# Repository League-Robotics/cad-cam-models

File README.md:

# Geared grippers

Two-jaw LEGO-compatible grippers driven by a pair of meshing 24T gears. The
gears are molded into short **gear arms** that stay in the frame. The jaws are
swappable **extension arms** that pin onto each gear arm's stub with two 2L
LEGO friction pins, 16 mm (2 studs) apart. The pins point at the other jaw, so
gripping pushes the arm further onto them.

## Printable parts: `grippers/`

| Folder | What | Parts |
|---|---|---|
| `arms/` | The gear arms on LEGO axles, shared by every set | `left_arm` (the Nezha motor's driven arm, cross hub), `right_arm` (the idler arm of every set: one plain 4.95 round hole, it turns on the axle the frame holds in cross holes; `idler_hub_pins` brings the four hub pin holes back) |
| `nezha/` | Gripper on the Nezha motor; uses both `arms/` | `frame` |
| `servo_standard/` | Gripper on a standard-size hobby servo; idler is `arms/right_arm` | `spline_arm`, `frame` |
| `servo_9g/` | Gripper on a 9 g micro servo; the frame top is a 3 × 5 block of pin holes, and the idler runs on a 3L axle; idler is `arms/right_arm`. `frame_centred` is the 2026-10-28 revision (`centred = true`): hole grid centred on the jaws (6 columns, the mesh on the 4th), full-unit back wall with 4 rows × 6 holes, the top plate a row longer with 6 holes out of its front face | `spline_arm`, `frame`, `frame_centred` |
| `extensions/` | Swappable arms; fit every set | `can_arm`, `cube_arm`, `cube_low_arm`, `cube_short_arm`, `ball_arm`, each `_left` and `_right` |
| `plates/` | One sheet of parts with first-layer sprues | `all_parts` |
| `brick_frame/` | The cage round the Nezha brick (`scad/brick_frame.scad`, 2026-11-02): four flat prints, each on its outer face, put together with 11 2L pins | `plate` (all four on one bed, 122 x 114), or one at a time: `side_j`, `side_iic`, `end_bar` (print two) |
| `pi_frame/` | The open frame round a Raspberry Pi (`scad/pi_frame.scad`, 2026-11-03): five flat prints, 8 2L pins; weld the Pi onto the base's posts | `plate` (all five on one bed, 114 x 164), or `base`, `window` (print two), `top_bar` (print two) |
| `huskylens_case/` | The LEGO tray for the DFRobot HuskyLens (`scad/huskylens_case.scad`, first draft 2026-11-14): one print, back face down, no supports; `views.png` is its four-view | `huskylens_case` |

Every STL is already in print orientation. The driven arm differs by motor
only in its hub: a LEGO cross-axle hole (`arms/left_arm`, Nezha) or a press-fit
spline socket (each servo set's `spline_arm`; the 9 g one is a plain 4.65 mm
hole). The idler arm is the same `arms/right_arm` everywhere.

- **Left / right:** the left extension arm goes on the driven gear arm (motor
  or spline), the right one on the idler arm.
- **Ball arms** stand on the cup and need supports under their base.
- **Cube arms** print on their outer face with the texture up.
- **Can arms** print flat.

| Arm | Holds | Closed at 0° |
|---|---|---|
| can | 66 mm can | 65 mm ring |
| cube | 26 mm foam cube | parallel paddles, 26 mm apart |
| cube_low | 26 mm foam cube, near the floor | as cube, but an open "racket" paddle (rim + diagonal ribs) 50 long × 62 tall: 16 mm further down and 8 up; swap left and right to put the 8 mm end down. On the Nezha frame it clears to ~29° open |
| cube_short | 26 mm foam cube, low mounts | as cube, paddle 32 tall (3 mm off each end), for mounts where the full paddle would reach the floor |
| ball | 40 mm ball | cylindrical cups, R 20.5 |

Clear opening, checked against frame and motor/servo for all three arms:

- Servo frames (standard and 9 g): 66°
- Nezha frame: 60°

## Viewing assemblies in the browser

`bash tools/make_views.sh [servo9g|nezha|plate] --open` builds self-contained
3D viewer pages in `view/` (three.js, STLs embedded, works from file://), one
checkbox and colour per component, and opens them in Chrome. Each assembly's
`show` parameter exports one component in place; `tools/mockup_html.py` (a part named with a leading `-` starts unticked, e.g. the can arms; a `pivot=x,y,sign` option makes it turn about that vertical axis with the Jaws slider) puts
them on one page. `bash tools/serve_views.sh` serves `view/` on http://127.0.0.1:8768/ so a page opens in VS Code's Simple Browser (file:// pages open as text there). `tools/bottom_view.py PART.stl OUT.svg` draws a part from
below on the 8 mm cell grid, for marking up changes.

## Sources

Carvera parts are moving to `/Volumes/Proj/proj/robot-projects/carvera/design/`
(read its `AGENTS.md`). The camera bracket (was `carvera_angle.scad`) and the
two-camera laser mount (was `laser_cam_mount.scad`) the dust-bay plate
(was `carvera_pi_bin.scad`) and the USB hub rack (was `usb_hub_rack.scad`) moved
there on 2026-11-06.

`scad/` holds the OpenSCAD sources:

| File | What |
|---|---|
| `gripper.scad` | Gear sector, original ring arm, Nezha 1U frame (library) |
| `swap_gripper.scad` | Gear arms (`nub` in the code) and the can / cube / ball extension arms. The can ring's rear ends (where it completes the circle inboard of the beam) are cut flat `ring_trim` (3.1) up from their lowest point so the closed arms clear the Cutebot gripper's caster beam (2026-10-29; 0 for the full ring), the cut meeting the base's inner face with a `ring_trim_r` (2) fillet. The ring is turned `can_ring_rot` (15) on the arm and then `can_ring_open` (5) about the axle relative to the stub (2026-10-29: the halves concentric with the arms 5 open), so gripper.scad's unchanged tips (10 mm thinned on opposite faces) meet on the centre line at theta 6.8, the halves are concentric at 5 and the tips lap fully at 4.3, the closing limit (past it the thick parts jam; the lap grows 3.9 mm per degree); `view/cutebot_can_ring.png` shows the ring closing |
| `nezha_gripper.scad` | Nezha set: assembly, parts, `clash` check |
| `servo_gripper.scad` | Servo sets (`servo = "standard"` or `"9g"`): assembly, parts, `clash` check; `jaw = "ring"` gives the old one-piece arms. `centred = true` (9 g, 2026-10-28, used by the block and Cutebot grippers): the hole grid centred on the gear mesh (`grid_z`, 6 columns about `mesh_z`; the axles sit 1.5 units off it, so the axle row keeps only the holes 12 from an axle), the wall behind the arm layer a full unit (`wall_t`) with a 4th row of holes (`lego_y`), the top plate's rows 3.9 in from the back face (`top_rows_x`: the axles 1.9 ahead of the first) and its front face one row further out at the gear teeth's reach, with blind holes (`front_hole_depth`, `front_skip`) in it for a caster or a part pinned on ahead. The default keeps the original frames unchanged |
| `lever_gripper.scad` | CONCEPT (2026-10-26): gearless gripper on a horizontal 9 g servo. Servo on edge, shaft forward between the jaw axles; vertical double horn with a ball on each tip; each jaw is a lever on a vertical axle with the swappable-arm stub and a fore-aft fork that straddles its ball (left jaw's fork over the upper ball, right jaw's under the lower one; both jaws are one part turned over). `phi` is the servo angle (-45 closed, +45 open, 53 deg of jaw); `show` = "all", "jaw", "clash", or one component. Pictures: `view/lever_gripper_concepts.png` (four concepts), `view/lever_gripper_mockup.png`, viewer `view/lever_gripper.html` |
| `swap_plate.scad` | The all-parts plate layout |
| `swap_plate_sprues.scad` | The plate's sprue bars (generated) |
| `lego.scad` | Include this for any LEGO Technic feature: pulls in `lib/Technic.scad` ([cfinke/Technic.scad](https://github.com/cfinke/Technic.scad): beams, pins, axles, connectors, gears) and adds `technic_pin_hole()` (exact LEGO hole, for models of real parts) and `pd_pin_hole()` / `pd_axle_hole()` (print-tuned holes from the League's Part Designer, lego3d.jointheleague.org; use these on anything we print) |
| `reflectance_sensor.scad` | The robots' 4-channel reflectance sensor with its LEGO brackets, from a scan (`models/reflectance_sensor_top_scan.stl` is a later scan of the board's top face, registered to the same coordinates on the bracket holes) (`part = "overlay"` shows `models/reflectance_sensor_scan.stl` over it); `pin_holes()` and `rs_holes` for parts that mount to it; the four cans' positions are from the top scan's solder-pad columns (2026-10-29), their TCRT5000 size from a photo |
| `front_plate.scad` | Sensor plate with the 9 g gripper frame built onto its front. Exact geometry only where something mates: the horns (the two beams into the robot), the gripper frame (arm bearing, pivot, idler axle, the servo's tab legs), the pin holes, the casters' seats, and pockets under the frame floor for what stands on the board's top (the sensors' clips, the button, two solder rows), measured on `models/reflectance_sensor_top_scan.stl`. Everything else is `models/front_plate_body.stl`, made by `tools/front_plate_body.py`: a smoothed hull-like lid with filleted posts down to the sensor, and the cable U, arm sweep and caster spaces carved out with rolled edges (re-run it with `uv run tools/front_plate_body.py` after moving anything it wraps). `part = "required"` shows the mating surfaces alone; `part = "control"` is just the control surfaces (the gripper frame, the horns, the servo tab seat, the sensor pads on the side brackets (pinned) and middle bracket (flat: the jack covers its holes), the caster seats, holes cut; print file `grippers/sensor_plate/control_surfaces.3mf` / `.stl`, `part = "control_print"`); `part = "clash_*"` checks it. Two LEGO EV3 ball casters (`models/ev3_ball_caster/`, SquareD's model, thing:622701, CC BY-SA) turned 90 degrees, slide on from the sides onto pins into seats beside the cable, set `caster_drop` (5 mm) below the robot's floor line so they bear on every robot Print files: `grippers/sensor_plate/front_plate_print.3mf` (clean manifold; prefer it) and `.stl`, frame floor down on the bed, support under the deck and horns |
| `robot_plate.scad` | The bought 11 x 19 Technic panel plate (LEGO 39369's shape: pin holes through every cell, a horizontal hole in from the face at every even cell round the edge) with the cut for the reflectance sensor, exactly on the cell edges: `hole = "3x4"` (columns 5-7, rows 5-8; the sensor under the plate, pinned at row 4 with its jack up through the hole and its PCB edge at the plate's front edge), `"3x3_9"` (the default and the one cut since 2026-10-30: 3x3 at rows 9-11, the sensor pinned at row 8; the user walked the hole back from 5-8 over four plates), `"cans"` (the sensor standing on top of the plate on its brackets, pinned at row 5 from below, with a pocket through the plate for its cans, one row behind the front so row 1's holes stay free, the middle two cans sharing one pocket since the 4.2 web between them did not survive the first cut, and the pockets' front edge 1.5 further forward (`can_front_ext`) since the cans did not clear it, the back edge 0.5 further back (`can_back_ext`) (2026-10-30); the cans at x = +-6 and +-30, 20.45 ahead of the bracket row, on the solder-pad columns of the top scan (2026-10-29), the body size still a guess, so `can_clear` is 1.0) or `"3x3"` (rows 6-8, the plate cut so far; its job ran 1.65 past the front cell edge, which is dropped). Cells count from the front-left corner, the plate held with its 19 side up and down. `part = "assembly"` puts the sensor in place; `"cam"` is the plate in the Carvera job's coordinates. Drawing: `view/robot_plates_drawing.png` (`tools/plate_drawing.py`), viewer `view/robot_plates.html` |
| `caster_post.scad` | The caster post (2026-10-28): a separate flat print for the grippers that stand on the EV3 ball caster ahead of the jaws (since 2026-10-29 every stance of the block gripper and the Cutebot gripper has one, its name etched in its top). Its back face is the centred frame's front face (the gear teeth's reach); two blind pin holes mate with the floor's front-face holes at x = +-8, two more in its front take the caster's pins; the post is a box from the floor's bed face or the beam's bottom up to the beam's top or the floor's top, with a pocket in its front for the caster's housing, which widens behind the beam face below the beam (`housing_prof`, from the caster model; the user measured its widest, 8.3), and `post_depth_for(floor_z, caster_top_z, min_depth)` makes it as shallow as the mating holes allow: `pin_wall` (0.8) between their bottoms and the pocket, or 8 + wall + 8 when they share a height band with the caster's pin holes (16.8), and at least `min_depth`: `post_min_depth(arm_z, caster_top_z)` gives `ring_post_depth` (17) when the beam is in the arm layer, which the closed can arms' trimmed ring ends need (so 17.0 on the Cutebot and the low stance, 17.55 on front, where the housing wants more). Also the caster model, `caster_on_post`, a 2L pin model and the mating pins. `caster_post(y_face, floor_z, pin_x, caster_top_z, min_depth, label)` in place, `caster_post_print` on its back face (every hole vertical) |
| `block_gripper.scad` | The 9 g gripper on the front of the two-plate robot (plates 3 units apart on the Nezha motors), since 2026-10-29 built from the Cutebot gripper's pieces: three flat prints pinned with 2L pins and glued. The frame is the centred 9 g frame turned over (the same print as the Cutebot's, unlabelled: floor of pin holes ahead of the robot, jaws centred on the plate with the axles at x = +-12, a full-unit back wall with 4 rows x 6 columns of holes facing the robot). The block (5 wide x 3 deep x 2 high; 3 with `sensor_mount = "under"`) sits between the plates on the front 3 rows, 10 pin holes down through its back two rows into the top plate (and the bottom plate when 3 high), and its front row given over to two rows of 5 blind holes in its front face that pin into two of the frame's wall rows. The frame's height is which wall rows meet the block's (`stance`: rows 8 apart, so the old 0 / 4.15 / 15.4 drops became 1 / 9 / 17): `"level"` the 2nd and 3rd rows (wall top 43, the floor 0.9 below flush, the top row pins into the top plate's edge holes at x = 0, +-16; cube paddles 16.4 off the ground), `"low"` the top two rows (wall top 35; the bottom row into the bottom plate's edge holes; paddles 8.4), `"front"` the top row on the block's lower row (wall top 27; the 3rd row into the bottom plate's edge holes; paddles 0.4). The caster post (`caster_post.scad`, one per stance with its name etched) pins into the floor's front-face holes at x = +-8 with the caster's beam top 28 over the ground: 16.8 / 17.0 / 17.55 deep. The can arms close clear of the caster in level and low (checked at theta 5 and 4.3); not in front, where the arm layer is under the beam and the ring's rear ends hit the housing's flare however the post is placed, so front is for the cube paddles. `sensor_mount = "top"` (the cans plate, the default; the block clears the sensor's parts) or `"under"` (the 3x4 plate). `part = "frame"` / `"block"` / `"post"` in place, `"print_*"` on the bed, `"clash"` / `"arm_clash"` / `"fit"` / `"caster_fit"` / `"block_fit"` check the arms / the arms against each other / the sensor / the caster / the block (`"clash_view"`, `"ring_view"` as the Cutebot's); `show` exports each component in place; `tools/robot_pics.py` makes `view/block_gripper_stances.png` (the three stances, labelled) and `view/block_gripper_pieces.png` (the prints); viewers `view/block_gripper_{level,low,front}.html` (the can arms unticked; Jaws slider) |
| `cutebot_gripper.scad` | The 9 g gripper on the front of the Elecfreaks Cutebot Pro, with its own caster (2026-10-28, replacing the user's hacked servo-kit gripper). Three prints, each flat, pinned together with 2L friction pins and glued: the frame (the centred 9 g frame turned over: floor of pin holes ahead of the nose, servo up, the full-unit back wall's 4 × 6 holes facing the nose; prints on its back wall; since 2026-10-29 the same print as the block gripper's, unlabelled), the tab (a 5-hole beam-shaped plate on the nose over its two bosses: counterbored M3 holes at x = +-8, pin holes at 0, +-16, and 5 pin holes in its front edge into one wall row, `tab_row`; prints flat) and the caster post (`caster_post.scad`, pinned into the floor's front-face holes at x = +-8, the EV3 caster on its front, "Cutebot" in its top; prints on its back face). Robot coordinates: X across, Y back from the nose's tip, Z up from the ground. `front_h` = 18.6 (the chassis PCB's underside at the front, measured, for level), `nose_t` = 1.5 (the PCB; the tab lies on it) and `boss_h` = 1.5 (the bosses stand proud, inside the tab's holes) set the tab's height, and with `tab_row` (the top row) the frame's height in steps of a wall row (`paddle_z0` echoed: 4.0); `boss_back` (13.5, a guess) the screw holes' row. `part = "frame"` / `"tab"` / `"post"` in place, `"print_*"` on the bed, `"clash"` / `"arm_clash"` / `"caster_fit"` check the arms against the pieces / each other / the caster (`"clash_view"` shows what the arms hit in red on the see-through assembly, `"ring_view"` colours the two swappable arms apart); `show` exports each component in place; `tools/cutebot_pics.py` makes `view/cutebot_gripper.png` (section, iso, the three prints) and `view/cutebot_can_arms.png` (the can arms closed: with `ext = "can"` they close clear of the caster, its post 17.0 deep and the ring ends trimmed, 2026-10-29); viewer `view/cutebot_gripper.html` (the can arms are in it unticked; its Jaws slider turns the arms about the axles). Prints in `grippers/block_gripper/` (frame, cutebot_tab, post_cutebot) |
| `brick_frame.scad` | FIRST DRAFT (2026-11-01/02): a cage round the Nezha brick (`models/nezha_breakout_v2.stl`), the edges of a box, for more attachment points and to turn it any way up, e.g. stood on its motor end at the front of a robot, display and switch forward, the micro:bit's USB end up. 11 x 11 units in plan, 6 high: a ring at the brick's bottom (pinned to it), a copy at its top (4.1 over the ridge) and a post up each corner. Across, the brick's 60 is centred in 88; each side is only its outer unit, leaving 6.2 between it and the brick all round for cables, bridged only by a pad at each of the brick's side pins (2026-11-02); along, its 80 plus one unit at the motor end. The micro:bit end has posts but no bars. Holes alternate along every edge, turned 90 degrees cell to cell: rails out / up from out at each corner, posts across / out, end bars along / up from along at the middle (the posts' tops have out twice, where two alternations meet). Each of the brick's four side holes has an arch in front that is a LEGO beam's rounded end, so the bottom rail's pad at each has a beam end (`tongue_r`, `tongue_clear`) in each arch with the pin's hole through it. Four flat prints pinned with 2L pins: the J and IIC sides (windows: bottom rail, top rail, two posts; mirror images) and the end bar (x2, 9 units, out to the sides; the bottom one pins into three of the brick's five end holes). The brick's own coordinates (x along, -40 the micro:bit end; +y the J side; bottom at z = 0); `stand = true` stands it up. `part` = `"assembly"`, `"side"`, `"end_bar"`, `"print"` (each on its outer face); drawings from `tools/brick_frame_pics.py` (`view/brick_side_holes.png`, `view/brick_frame_cage.png`, `view/brick_frame_plan.png`, `view/brick_frame_stand.png`); viewers `view/brick_frame.html` and `view/brick_frame_stand.html` |
| `tilt_table.scad` | (2026-11-01) A hand-set friction tilt table for small cameras (Pi / Arduino camera boards). Two 5 x 5 plates, the same print twice, the second turned over; each has triangles standing up on its two hinge edges, apex at the axis: a fork (+x: two 2.5 tines, a 3.5 slot, a divot in each tine's inner face) and a tongue (-x, where the slot would be: 2 * `squeeze` (0.1) thicker than the slot, a 45 deg cone bump, r 2.5, 0.4 high, on each face). Turned over, each plate's tongue snaps into the other's fork: the tines clamp it, the bumps in the divots are the pivot, the squeeze is the friction. (The first draft, one ear in and one out per plate, did not clamp: the plates slid apart sideways.) Third version (2026-11-03, after the second print popped apart: the 0.4 bumps never seated, the tongue 0.2 over the slot bowed the tines out, the 0.2 teeth printed as a texture): a hole through each tine on the axis (r 2.75) instead of a divot, buttons 1.2 high (r 2.6, sides 50 deg off the face), `squeeze` 0, and teeth with 35 deg flanks from r 4.5 to r 9 (0.4 to 0.8 high), the grooves `click_clear` 0.1 deeper; between clicks each tine spreads up to 0.74 and the buttons stay 0.46 in. Fourth version (2026-11-03, the third snapped well but locked: barely movable, and not back from the limit without pliers): the teeth half as high, `click_flank` atan(tan 35 / 2) = 19.3 deg (0.2 to 0.4 high); between clicks each tine spreads up to 0.37, the buttons stay 0.83 in. The first print worked as wanted (2026-11-01). Clicks (2026-11-01): `clicks` (24) radial teeth round the axis, 15 deg apart (flat is one), `click_h` (0.2) high, from r 3 to r 7, raised on the tongue's faces and sunk as grooves in the tines'; at a click each ridge sits in a groove (just the squeeze), between clicks they spread each tine another 0.2; `clicks = 0` is the smooth table. Triangle outline (2026-11-01, fit and finish): the room the other plate leaves as it tilts, less `roll_gap` (0.4): an arc r 11.8 round the axis over the top (the other plate's underside rolls round it) and straight sides the other plate lies parallel to at the +-63 limits, landing 19.35 out (the first print had an r 6 apex and sides from the corners). Prints 31.6 tall. Knobs: `click_flank` (click strength), `clicks` (must be even), `squeeze`, `bump_h`, `tine_t`. Plates `pitch` (4) units apart when flat (a 5 x 5 x 5 block), tilt +-63 (the plates meet). Pin holes have Part Designer's taper on the bed (mounting) face; the two columns under the triangles are blind, 8 deep from that face. `part` = `"plate"` (the print), `"print"` (two on the bed), `"assembly"` (at `theta`), `"clash"`, `"bottom"` / `"top"`; prints `grippers/tilt_table/` (`make_parts.sh tilt_table`: plate, plate_x2, plate_smooth); drawing `view/tilt_table.png` (`tools/tilt_table_pics.py`); viewer `view/tilt_table.html` (Tilt slider) |
| `pi_frame.scad` | FIRST DRAFT (2026-11-03): an open frame round a Raspberry Pi, the Nezha cage's 11 x 11 footprint, 5 high, the edges of a box with holes on every face. The Pi lies flat, centred, 13.8 up on four weld posts copied from the user's Yahboom encoder mount (verified to fit: a 6 mm support 6 tall and a 2.4 mm pin 3 tall, melted down over the board; 57.7 x 48.5 apart, a little under the Pi's published 58 x 49), standing on two deck bars across the bottom at y = +-24; its USB and Ethernet face out of the +x end window (0.8 past the face, 1.0 under the top bar), power and HDMI out of a side window. Holes alternate cell to cell as on the cage (5 high lets the posts alternate cleanly). Five flat prints, three designs, pinned with 8 2L pins: the base (end bars, deck bars, weld posts), the window (x2, one print) and the top bar (x2). `part` = `"assembly"`, `"print"`, `"print_base"` / `"print_window"` / `"print_top_bar"`; drawings `tools/pi_frame_pics.py` (`view/pi_frame_views.png`, `view/pi_frame_plate.png`), viewer `view/pi_frame.html` |
| `huskylens_case.scad` | FIRST DRAFT (2026-11-14): a LEGO tray for the DFRobot HuskyLens (SEN0305), one print, 71.6 x 55.6 x 15.6 (two units deep). The board drops in screen up between two columns (5 pin holes each, front to back, at x = +-32; 4 in the first draft, 5 the same day at the user's word) and lies camera down on two ledges and the neck behind its tab, where two M3 screws go through the tab's holes into 4 mm holes (heat-set inserts, or bolts and nuts). Under the tab, between the USB and UART cables, a 3 x 2 bar: its middle cell's hole runs front to back, the outer cells' four holes come up from underneath (to stand it on a plate). The floor is a 1.6 plate behind the board with a notch for the camera (2.6 inside the back face); the floor stops at y = 14.8, below the function dial and the learn button; the columns run to y = 24, beside them. All board numbers are from the GrabCAD STEP model (`models/huskylens/`, not checked against the real board). Open: the right column covers the microSD slot. `part` = `case`, `print`, `assembly` (with `show` = `case`, `board`, `parts`, `screws`), `clash`. Viewer `view/huskylens_case.html` (`make_views.sh huskylens`), drawing `view/huskylens_case_drawing.html` (`tools/huskylens_pics.py`) |
| `raspberry_pi.scad` | An approximate Raspberry Pi 4 (board, holes, blocks for the connectors that set clearances) from the published mechanical drawing, for laying out frames: `raspberry_pi4()` |
| `tt_motor_red.scad` | FIRST DRAFT (2026-11-08): the Red TT motor with its encoder cover, the checked gearbox (`models/tt_motor/tt_gearbox.stl`) plus a modelled motor end (three sections, each a circle cut by two flats, and the connector block); the Blue TT is the same without the cover. `show` = `"gearbox"` or `"motor"`. Dimension sheet: `view/tt_motor_dims.html` (`tools/tt_motor_dims.py`). `part` splits it into four glued prints, front and back on Y = 0 and gearbox from motor at Z -25.21: `gearbox_front`, `gearbox_back`, `motor_front`, `motor_back`, each cut face down as `print_*` (`tt_motor/red_print/`), located by loose square pins and a tongue on the motor end in a slot in the gearbox; viewer `view/tt_red_print.html` |
| `tt_motor_case.scad` | MOCKUP (2026-11-08): LEGO cases for the Red TT motor, `cells` = 3 or 5 units high, 11 long. The motor lies along an 11 x 19 plate, shaft out of the robot, connector inwards; a back row of pin holes one unit deep stands on the plate and the motor hangs off its edge. 3 units: 0.75 side walls, notched round the 25 mm bulge; the cap holds by friction pegs (`retain = "pegs"`) or M3 self-tappers (`"screws"`) into the blocks past each end of the motor. 5 units: 8.6 rails above and below with pin holes on their faces; the cap has four hook arms inside the rails that click into windows. `part` = `body`, `cap`, `motor`, `plates`, `print_body`, `print_cap`, `clash_body`, `clash_cap`. Viewers `view/tt_case.html` (`make_views.sh ttcase`) |
| `models/huskylens/` | The DFRobot HuskyLens (2026-11-14): `HuskyLens.step` from GrabCAD (grabcad.com/library/df-robot_ai-huskylens-gravity-sen0305-1, a user's model), and two meshes made from it with FreeCAD, `huskylens_board.stl` (board, screen, camera) and `huskylens_parts.stl` (buttons, sockets, chips), in the STEP's frame: board centre line on x = 0, board z = 0 ... 1, camera towards +z, screen towards -z |
| `models/tt_motor/` | TT gearmotors (2026-11-08). `tt_gearbox.stl` is the gearbox and shaft the user checked against real motors (2026-11-08), one solid, Z -25.21 to +16.5, in the frame below; `tt_gearbox_original.stl` is the same mesh where it was exported. `tt_case_ref_1` and `_2` are the "TT Motors & Wheels" models a printed case proved against real motors (1 a plain TT with its clip, 2 a closed barrel with a connector block), with `_aligned` copies in the shared frame: origin on the shaft at mid-thickness, X across, Y along the shaft (nub on -Y), motor at -Z. `adafruit_3777_*` and `adafruit_3802_*` are Adafruit's plastic- and metal-gear models (MIT, Adafruit_CAD_Parts);  `uv run tools/tt_motor_dims.py` draws the numbered dimension sheets, `view/tt_motor_dims.html`; caliper corrections go in its `CORRECTIONS` |
| `models/` | Reference models the sources import: Nezha frame and motor, standard servo. `servo_9g.stl` is kept for reference only: its heights are wrong, so the 9 g servo is modelled from caliper measurements (`servo_9g_dims.png`). `nezha_breakout_v2.stl` is the ELECFREAKS Nezha Breakout Board V2 (the "brick") with its micro:bit, one low-poly solid for laying out robots (2026-11-01): the envelope caliper-measured, 80 front to back x 60 x 43.7 high, the micro:bit shelf 31.5 and the button's surface 40 up (`nezha_breakout_v2_dims.svg`), its Technic holes (8 mm pitch, 4.0 above the bottom; on each long side two normal holes, each behind an arch open to the bottom edge (all four alike, 2026-11-02), 1.86 deep, the user's measurement, exactly a LEGO beam's rounded end: Technic.scad's beam width, 7.36) and 4P4C sockets (12.8 pitch) measured on a 3D scan; `nezha_breakout_v2.glb` is the same in colour for viewers. Both are made by `tools/nezha_breakout.py` (manifold3d; every dimension is a named constant at its top; the button is modelled off, `BUTTON_ON` for on) |

`cam/` holds the Carvera G-code for the plates' cuts, from `tools/plate_gcode.py`
(the job of `CAM/RobotPlate/robot_plate.nc`: 2 mm corn cutter, T1 since
2026-10-30 (T3 in the first job), 12000 rpm, 500 / 300 mm/min, 0.3 mm passes
through the 7.7 mm plate, contours with 2 mm tabs (the first plate's 1 mm tabs let every slug but the 3x4's pop out); Z probe at X40 Y24 from the
work origin, a cell corner below and ahead of the hole): three one-plate jobs, `plate_hole.nc` (the 3x3 sensor hole at rows 9-11),
`plate_pockets.nc` (the can pockets, the middle two run together) and `plate_hole_and_pockets.nc`
(both). Origin at the plate's front-left corner, front edge on X = 0. The
script can also lay plates out two by two (`--nx 2 --ny 2`, 302.4 x 176 mm)
or stack two (`--layers 2`, unverified: the tabs hold only the bottom piece
and the cutter needs the reach).

`tilt9g/` is the 9 g frame as a tilt table. `tilt9g.scad` includes
`servo_gripper.scad` and adds three LEGO units under the servo: a plate, an
arm layer for a flipped idler arm (`arms/right_arm`) on the spline axis, and a second plate. With
the gripper's idler arm left out, the spline arm folds flat, and a plate
pinned across both stubs tilts about the spline axis (θ −110 to +50, flat at
−90). Since 2026-10-31 the frame holds the bottom 3L axle still in cross holes
(P1, P2) and the bottom arm turns on it, as in the 9 g gripper; the table is a
printable 3 × 7 plate of pin holes. `pan9g.scad` is the camera pan head that
pins to the table's middle 3 × 3 (tilt first, then pan): the 9 g servo upside
down in the pan frame, an L (2026-10-31): a top over the servo's bottom end
with 4 × 5 pin holes for the camera and one side, a unit thick, down the
servo's length with 4 × 5 (the shared corner row alternates top, side, top,
side, top); just a tab-wide leg under each tab for its screw, solid down to
the top, the wire turning out the open side in a groove in the wire-end
leg (`view/tilt_pan9g_wire.png`); prints on the pin side's face. Its spline pressed into a 3 × 3 spline
plate (round 4.65 socket 3.5 deep, a 1.2 shelf, the horn screw from the
table side with its head in a 4.6 counterbore; no tube and recess). The pan
axis is 5.4 off the camera grid's middle column. `bash tilt9g/export.sh`
writes the prints (`frame.stl`, `table.stl`, `pan_frame.stl`,
`spline_plate.stl`, all in print orientation) and the `view/` meshes;
`make_views.sh tiltpan` builds `view/tilt_pan9g.html` (table flat, Pan
slider) and `view/tilt_pan9g.png` is the labelled section. The
`tilt9g-viewer` launch entry (or `python3 -m http.server 8767 --directory
tilt9g`) serves `index.html`, an animated three.js view, at
<http://localhost:8767/>.

`solidcraft/` holds the SolidCraft designs: `gripper_9g.solidcraft` is the 9 g
gripper as a jointed assembly (servo, frame, both gear arms, axle) with a `Grip`
motion study, and `gripper_9g.gif` its animation. The MCP server in
`.mcp.json` may save into this folder.

`tools/` holds the scripts:

| File | What |
|---|---|
| `make_parts.sh` | Exports every STL into `grippers/` (`block_gripper` set, the pinned grippers since 2026-10-29: `grippers/block_gripper/frame.stl` (one frame for every robot, on its back wall), `block.stl` (the two-plate robot's mount, flat), `cutebot_tab.stl` (flat), `post_{level,low,front,cutebot}.stl` (on their back faces); `servo_9g` set also `frame_centred.stl`) |
| `front_plate_body.py` | Builds the front plate's smooth connecting body (distance fields, smooth union, marching cubes) into `scad/models/front_plate_body.stl`; run with `uv run` |
| `plate_sprues.py` | Picks the plate's sprue bars; run it after moving parts on the plate |
| `plate_gcode.py` | Carvera G-code for the robot plates' cuts (`cam/`): `--hole 3x3|3x4|3x3_9|cans|<hole>_cans --nx --ny --layers --gap --tool --tool-number --step --feed --plunge` (defaults: the 2 mm corn cutter job); `3x3_9_cans` is both cuts in one plate |
| `plate_job_pic.py` | A plate job's toolpath drawn on the cell grid (`view/robot_plate_3x4_cans_job.png`) |
| `plate_drawing.py` | `view/robot_plates_drawing.svg/.png`: both plates cell by cell with the sensor, and the Carvera lay-up |
| `robot_pics.py` | Labelled pictures of the block gripper (`uv run --with pillow tools/robot_pics.py [stances] [pieces]`): `view/block_gripper_stances.png` (side section and front view of each stance, which wall rows take the pins, the level assembly from the front-left) and `view/block_gripper_pieces.png` (the prints on the bed) |
| `cutebot_pics.py` | Labelled side section, iso and the three prints of the Cutebot gripper (`uv run --with pillow tools/cutebot_pics.py`): `view/cutebot_gripper[_side|_iso|_parts].png`, and the closed can arms over the caster, `view/cutebot_can_arms[_top|_side].png`; reads the scad's `echo()` values for the dimensions |
| `brick_frame_pics.py` | Labelled drawings of the Nezha brick's side holes and the cage round it, cut from the meshes (`uv run tools/brick_frame_pics.py`): `view/brick_side_holes.png`, `view/brick_frame_cage.png`, `view/brick_frame_plan.png`, `view/brick_frame_stand.png` |
| `pi_frame_pics.py` | Labelled drawings of the Pi frame (`uv run tools/pi_frame_pics.py`): `view/pi_frame_views.png` (above, side, USB end) and `view/pi_frame_plate.png` |
| `viewer3d/` | The Robot Garage 3D viewer (wiki: cad-design-projects/3d-viewer; On / Ghost / Off per part, Explode, Section, Measure), for new assemblies: `template.html` is the USB Power Switch viewer's page with its part list and sizes taken from the page's data, `pack.py CONFIG.json OUT.html` packs the STLs in; one `<name>.json` per page (`huskylens_case.json`), built by `make_views.sh` |
| `huskylens_pics.py` | Drawings of the HuskyLens tray (`uv run tools/huskylens_pics.py`): `grippers/huskylens_case/views.png` and the labelled `view/huskylens_case.png` |
| `scad_view.py` | Live browser viewer: re-exports the parts in `view/targets.txt` whenever a `.scad` file is saved |

Both scripts work from any directory. To rebuild everything, or just some
sets, run:

```bash
bash tools/make_parts.sh
```

```bash
bash tools/make_parts.sh servo_9g extensions
```

### Live viewer

`tools/scad_view.py` serves `view/` with the Buzzkill viewer
(`tools/buzzkill/serve.py`) at <http://localhost:8766/> and watches `scad/`.
On every save it exports each target in `view/targets.txt` to
`view/<name>.stl`, and the page reloads the newest one. The `scad-viewer`
entry in `.claude/launch.json` starts it in the Claude app's browser sidebar.
To run it from a terminal instead:

```bash
python3 tools/scad_view.py
```

`view/targets.txt` takes one `name: file.scad var=value ...` line per part.
Each `var=value` becomes an OpenSCAD `-D` override, and the file is re-read
on every change:

```
left_arm: scad/gripper.scad part="left"
nezha_frame: scad/nezha_gripper.scad part="frame"
```

A failed export prints the OpenSCAD errors and leaves the last good STL in
place.

## Circuit boards: `pcb/`

The Carvera-milled PCBs, brought in on 2026-11-03 from the standalone
`/Volumes/Proj/proj/CAM/nezha-qwiic` repo (its history stays there). See
[pcb/README.md](pcb/README.md): the Nezha 4P4C-to-Qwiic adapter (top level),
`wire-hub/`, and `plug-tail/` (boards that slide into the back of a 4P4C plug,
for servos and Qwiic). KiCad 9, pcb2gcode and the build scripts run on Buzzkill
(`ros@buzzkill.local:~/projects/nezha-qwiic`); copy results back here.
`uv run tools/plug_tail_pics.py [STOCK_MM]` draws the plug tail in the cable
cavity (`view/plug_tail_section.png`); `bash tools/make_views.sh plugtail` builds
`view/plug_tail.html`, both tails in 3D with a checkbox per layer (F.Cu, mask, paste,
silk, fab, courtyard, Edge.Cuts) plus the isolation and outline cuts read back from the
Carvera program. Refresh `pcb/plug-tail/exports/layers.json` with
`scripts/dump_layers.py` on Buzzkill after the boards change.

## `archive/`

Earlier work, kept for reference:

- the one-piece ring arms and their renders
- the old servo arm STLs
- the motor brackets
- the Tinkercad reference files
- the first `stl_swap` export
- a backup of the SCAD files from before the swappable-arm refactor

Paths inside the archived files were not updated.

## Headless SolidCraft on Buzzkill

`.mcp.json` also defines `solidcraft-buzzkill`: the SolidCraft MCP server run
headless on Buzzkill over ssh (`tools/buzzkill/solidcraft-remote.sh`). It reads
and writes `~/designs/gears` there. Meshes exported into
`~/designs/gears/view/` show up live at <http://buzzkill:8765/> (three.js
viewer, follows the newest file). `tools/buzzkill/sync.sh deploy` copies the
scripts to Buzzkill; `sync.sh pull` copies saved designs into
`solidcraft/buzzkill/` to open in the Mac app.

`solidcraft-buzzkill-gui` drives the full SolidCraft app instead, running on
Buzzkill in a virtual display (`tools/buzzkill/gui.sh`: Xvfb `:77`, control
port 7878, x11vnc, noVNC). Everything listens on Buzzkill's localhost;
`tools/buzzkill/sync.sh vnc` starts it and tunnels noVNC to
<http://localhost:6080/vnc.html?autoconnect=1&resize=scale>.

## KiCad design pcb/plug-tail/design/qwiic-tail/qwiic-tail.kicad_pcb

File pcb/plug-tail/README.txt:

NEZHA 4P4C PLUG TAILS - REVISION C - 2026-11-04

REV C (the user, 2026-11-04): the servo tail is now the HEADER TAIL
(design/header-tail), 10.0 x 19.0, with all FOUR lines out on four flat 2.54
pins in plug-contact order: GND, VCC, S1, S2 (cable black, red, green,
yellow). A servo plug goes on G V S1; a J-port device uses all four. Program
cam/plug-tails-C-4up-iso120-cut155.nc, area 53 x 30. Rev B is in
archive/rev-B; the 3-pin servo tail's files were moved out of the live tree.

REV B (the user, 2026-11-04): the narrow tongue is 10 mm long, not 6, and the
pin pads run 10 mm along it (0.25-10.25 from the tip), so the wires/pins from
the plug have more length on the board. Everything behind the tongue moved
4.8 mm back (4 for the tongue + 0.8 so each trace bend stays 0.75 past the
pads, as in rev A). Servo tail 8.0 x 19.0, Qwiic tail 9.0 x 24.0. Program
cam/plug-tails-B-4up-iso120-cut155.nc, area 49 x 30. Rev A is in archive/rev-A.
The rest of this file was written for rev A; its sizes are rev A's.

A sliver of board that slides into the cable cavity at the back of a 4P4C
plug. Four square header pins (0.64 mm, double length) lie in the plug's wire
channels where the cable conductors would be, and are soldered flat onto the
board's pads. The board then carries the signals out to a different
connector. Two tails share the same plug end:

 servo-tail  8.0 x 14.2 mm  three flat 2.54 mm pins for a servo plug (G V S)
 qwiic-tail  9.0 x 19.2 mm  side-entry JST SH (Qwiic) socket, 0R crossover

Everything is surface-mount on ONE copper layer, the top. No holes, no vias.

PLUG END (both boards)
Tongue 5.30 mm wide x 6.0 mm long, for a cavity measured at about 5.5 x 3.15.
Pin pads: 4 at 1.02 mm pitch (the standard 0.040 in modular-plug spacing),
0.62 mm wide, 0.40 mm gaps, running 0.25-3.60 mm from the tongue tip.
The tongue tip goes in first and stops against the wall where the wire
channels start; the tongue is longer than the cavity is deep, so the step
where the board widens may stand a little proud of the plug's back face.
The 0.8 mm cutter leaves a 0.4 mm radius in the two inside corners at the
root of the tongue. No retaining tab is placed on the tongue.

Pad order, copper face toward the plug's CONTACTS, plug nose pointing away,
left to right: contact 1, 2, 3, 4.
 I2C port (from the first adapter): GND, 3V3, SCL, SDA.
 Servo port: ASSUMED GND, V, SIG, unused. NOT VERIFIED - see below.

ASSUMPTIONS TO CHECK BEFORE CUTTING
1. Servo port pinout and voltage. The servo tail routes contact 1 -> G,
   contact 2 -> V, contact 3 -> S and leaves contact 4 unconnected. Meter a
   servo port (or its cable) and say which contact is which, and what voltage
   is on V. If V is not between G and S in contact order, the single copper
   layer needs a crossover like the Qwiic tail's.
2. Pin pitch. 1.02 mm centre to centre, so pins 1 and 4 are 3.06 mm apart
   centre to centre, 3.70 mm across their outside edges. A 4.0 mm reading
   would mean 1.12 mm pitch; that is one constant in scripts/build.py.
3. Board thickness. Copper-up board under the pins: the board's top must sit
   at the underside of the pins. With 1.4 mm stock the pins ride 1.4 mm
   above the cavity floor and the stack (board + pin) is 2.04 of the 3.15 mm.
   Measure cavity floor to pin underside; thinner stock may be needed.
4. Cavity depth (back face to channel wall). The tongue is 6.0 mm long and
   the pads cover the first 3.6 mm; the pins need to lie on that stretch.
5. Which side of the pins the board sits. Board UNDER the pins with copper
   facing the contacts is assumed. If it has to go above them, copper facing
   the latch, the pad order reverses: mirror the layout.

ASSEMBLY (suggested order)
a. Solder the four pins flat on the tongue pads first, outside the plug,
   with the pins overhanging the tongue tip by the channel length.
b. Feed the pins into the plug's wire channels and slide the tongue into
   the cavity until the tip stops.
c. Crimp. The contact blades bite the pins and the strain-relief bar clamps
   the board. Check that all four contacts are pressed flush; a blade that
   stops on a solid pin and stands proud can jam the jack.
   (Crimping first and then sliding the board in also fits the geometry,
   but the joints are then soldered inside the cavity mouth.)
d. Servo tail: lay three 0.64 mm square pins on the 1.0 x 5.0 mm pads, with
   about 6 mm overhanging the end for the servo socket, and solder them.
   Standard pins pulled from a header are long enough; trim double-length
   ones to about 11 mm. Servo plug: brown/black on G, red on V, orange on S.
   Qwiic tail: fit R1 (insulated-body 0R 1206) and the SM04B socket,
   including both anchor tabs. R1 carries SCL over the SDA track.
e. Milled boards have no solder mask and the copper around the tracks is
   left in place (floating). Keep solder off it; check every pair of
   signals for shorts and each signal for continuity before power.

PARTS (per board) - see parts.csv
 Both:  one 4P4C plug; four 0.64 mm square double-length header pins.
 Servo: three more 0.64 mm square pins.
 Qwiic: JST SM04B-SRSS-TB(LF)(SN) side-entry socket; YAGEO RC1206JR-070RL.
 The Qwiic socket here is the HORIZONTAL SM04B, not the BM04B top-entry
 part used on the first adapter.

MACHINING - see cam/READ-ME-FIRST.txt
 cam/plug-tails-A-4up-iso120-cut155.nc: 2 servo + 2 Qwiic tails in a
 49 x 25 mm free area, copper up, G54 at that area's lower-left corner.
 Offline checks: cam/validation.json. Not test-cut.

FILES
 design/servo-tail, design/qwiic-tail  KiCad 9 projects
 exports/assembly-preview.pdf           both boards with pins and labels
 exports/<board>/schematic.pdf          schematics
 exports/<board>/fabrication/           Gerbers for a board house (F.Cu)
 exports/<board>/milling/               simplified Gerbers used for CAM
 checks/                                geometry, ERC, DRC, netlists

REGENERATION ON BUZZKILL (ros@buzzkill.local:~/projects/nezha-qwiic/plug-tail)
 python3 scripts/build.py          CAD, from the constants at its top
 python3 scripts/export.py         ERC/DRC (fails on any violation), Gerbers
 python3 scripts/make_cam.py       pcb2gcode isolation + generated outlines
 python3 scripts/check_and_draw.py independent checks, drawings
KiCad 9.0.8, pcb2gcode 3.0.4, Shapely 2.1.2. build.py overwrites the CAD.

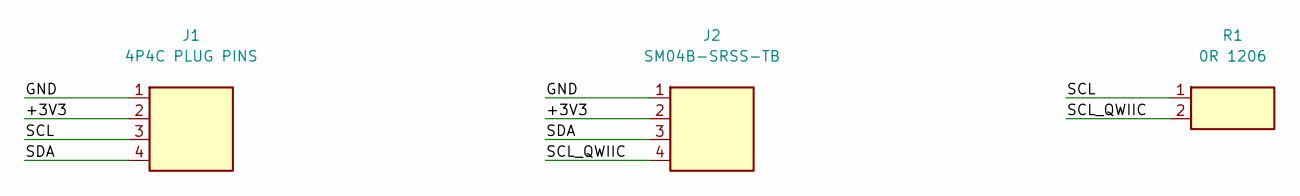
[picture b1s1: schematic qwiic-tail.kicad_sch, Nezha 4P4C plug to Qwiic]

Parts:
J1: 4P4C PLUG PINS; PlugPins_1x04_P1.02_SMD
J2: SM04B-SRSS-TB; JST_SH_SM04B-SRSS-TB_Horizontal
R1: 0R 1206; R_1206_3216Metric

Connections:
/+3V3: J1.2, J2.2
/GND: J1.1, J2.1
/SCL: J1.3, R1.1
/SCL_QWIIC: J2.4, R1.2
/SDA: J1.4, J2.3

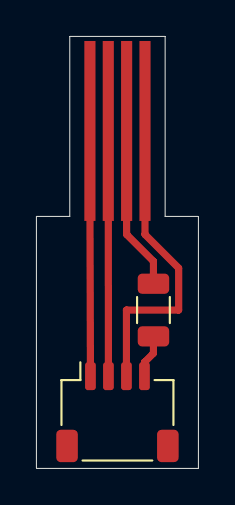
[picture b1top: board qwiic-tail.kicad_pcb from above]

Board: 2 copper layers, 9.0 x 24.0 mm, 3 parts (0 on the bottom side), 5 nets.

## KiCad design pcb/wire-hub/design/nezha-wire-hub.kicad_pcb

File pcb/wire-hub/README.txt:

NEZHA WIRE HUB - REVISION A - 2026-10-29

A 26 x 16 mm passive 3.3 V I2C adapter, separate from the earlier 4P4C-jack
adapter. Project: /Volumes/Proj/proj/CAM/nezha-qwiic/wire-hub/

CONNECTIONS
J1: four stripped cable wires; insert from top and solder underneath.
J2: four-position 2.54 mm FEMALE through-hole header, on top.
J3: four-position 2.54 mm MALE through-hole header, on top.
J4: four-position 2.00 mm JST PH through-hole socket/header, on top.
J5: four-position 1.00 mm JST SH/Qwiic surface-mount socket, underneath.
The four wire holes and all four connectors are electrically in parallel.
All solder joints and all manufactured copper are on the BOTTOM.

Every connector uses pin 1=GND, 2=3V3, 3=SDA, 4=SCL.
Viewed from TOP with wire holes on the LEFT, wire holes run top-to-bottom:
BLACK (GND), RED (3V3), YELLOW (SDA), GREEN (SCL).
Spread the two loose signal wires into their labeled holes; do not copy the
black/red/green/yellow physical order of the telephone plug contacts.
This removes the need for a crossover resistor. No active parts or pull-ups.
J4 PH uses this board's stated pinout; PH itself does not define a signal order.
Use 3.3 V I2C ports. This is not a motor-power or 5 V level-conversion adapter.

PARTS
One each per board; 25 each for a completely populated sheet:
J2 Harwin M20-7820442 (female, 2.54 mm, 8.5 mm body height).
J3 Harwin M20-9990446 (male, 2.54 mm, vertical).
J4 JST B4B-PH-K-S(LF)(SN) (PH, 2 mm, vertical through-hole).
J5 JST BM04B-SRSS-TB(LF)(SN) (SH, 1 mm, top-entry SMT).
J5 is the same selected part as the older adapter. The standard JST SH/Qwiic
PCB sockets are SMT; no through-hole substitute is used.
See parts.csv for supplier links. No purchasing/cart changes were made.
Optional PH mating cable: PHR-4 housing with compatible JST PH contacts or a
preassembled PH cable; verify its pin order before using it.

HOLES AND FOOTPRINTS
16 unplated solder holes per board. No vias or plated barrels are required.
Wire holes: 1.10 mm diameter, 2.10 mm lands, 2.54 mm pitch.
Male/female header holes: 1.05 mm diameter, 2.00 mm lands, 2.54 mm pitch.
The Harwin female drawing calls for 1.02 +/- 0.05 mm finished holes.
PH holes: 0.90 mm diameter, enlarged 1.60 x 2.00 mm oval/rectangular lands,
2.00 mm pitch. The PH hole is intentionally larger than the standard KiCad
0.75 mm hole to allow milling with the existing 0.8 mm corn bit. Check the
first connector's fit before populating the sheet. Minimum PH annulus 0.35 mm.
The Qwiic land pattern retains KiCad/JST dimensions, including both anchor tabs.
Main tracks 0.60 mm wide; Qwiic fanout tracks 0.40 mm. No copper pours.

KiCad represents the solder holes using through-hole electrical pads with
unused layers removed and Keep Top/Bottom disabled. All top annuli are
suppressed, confirmed by the validation script. The fabrication drill file
explicitly marks all holes NON_PLATED. The pads remain connected on B.Cu.

FABRICATION / CAM ORIENTATION
The editable design and fabrication Gerbers use normal TOP-view coordinates.
Fabrication: one bottom copper layer; 26 x 16 x 1.4 mm; all holes unplated.
Ask a fabricator to quote this single-sided specification; it is not a
conventional two-layer plated-hole ordering preset.

The separate machining-only artwork is mirrored ONCE to show bottom copper
face-up. The machine transform from top-view board coordinates is:
X = board-placement-X + 26 - top-X
Y = board-placement-Y + 16 - top-Y
Do not mirror the CAM Gerbers or finished G-code again.

PANEL
25 boards, 5 columns by 5 rows, in fresh 150 mm X by 100 mm Y stock.
Board width 26; height 16; gutters 2; nominal border 6 mm on every side.
Lower-left origins X = 6,34,62,90,118; Y = 6,24,42,60,78 mm.
Each board has four 2 mm-wide tabs retaining 0.5 mm thickness.
The board outlines occupy X6..144 / Y6..94; cutter sweeps extend to
approximately X5.2..144.8 / Y5.2..94.8. Clamp and dust-shoe clearance must
extend beyond that envelope. Full-area flat tape support is preferred.
See cam/READ-ME-FIRST.txt before using either machining file.

ASSEMBLY
Use exports/assembly-preview.pdf for top/bottom orientation.
Deburr the holes and edges, remove isolation debris and clean the copper.
Fit the bottom SMT Qwiic socket first, including both mechanical anchors.
Insert top headers and PH connector, then solder their pins on the bottom.
Keep solder fillets clear of adjacent exposed tracks; milled boards have no
solder mask. Insert/tin/trim the four wires and solder them in the labeled order.
Secure the cable jacket to the board/enclosure so pulls do not load the joints.
Check all five connectors for continuity on each signal, and check all six
signal pairs for shorts before connecting power. Verify the actual Nezha
cable with a meter; the photographs do not establish electrical continuity.

FILES
 design/nezha-wire-hub.kicad_pro - editable KiCad project
 design/nezha-wire-hub.kicad_sch - schematic
 design/nezha-wire-hub.kicad_pcb - individual board
 exports/schematic.pdf - schematic drawing
 exports/assembly-preview.pdf - annotated top and bottom views
 exports/fabrication/ - single-board Gerbers and unplated drill file
 exports/milling/ - mirrored-once machining input files
 cam/panel-layout.pdf - full-stock layout
 cam/validation.json - offline checks and final NC hashes
 parts.csv - board BOM with 1-board and 25-board quantities
 references/ - manufacturer drawings and source URLs

REGENERATION ON BUZZKILL
Working copy: /home/ros/projects/nezha-qwiic/wire-hub/
 python3 scripts/build_wire_hub.py
 python3 scripts/export_wire_hub.py
 python3 scripts/make_cam.py
 python3 scripts/check_and_draw.py
 python3 scripts/package.py
Build regenerates CAD; preserve manual edits before running it again.
KiCad 9.0.8, footprint library 9.0.7, pcb2gcode 3.0.4 and Shapely 2.1.2.

REFERENCES
JST SH: https://www.jst-mfg.com/product/pdf/eng/eSH.pdf
JST PH: https://www.jst-mfg.com/product/pdf/eng/ePH.pdf
Qwiic pinout: https://www.sparkfun.com/qwiic
Harwin: https://www.harwin.com/products/M20-7820442
Harwin: https://www.harwin.com/products/M20-9990446
Makera: https://wiki.makera.com/en/carvera/manual/software
KiCad library-derived JST geometry retains its upstream license; see
 design/KICAD-LIBRARY-COPYRIGHT.txt.

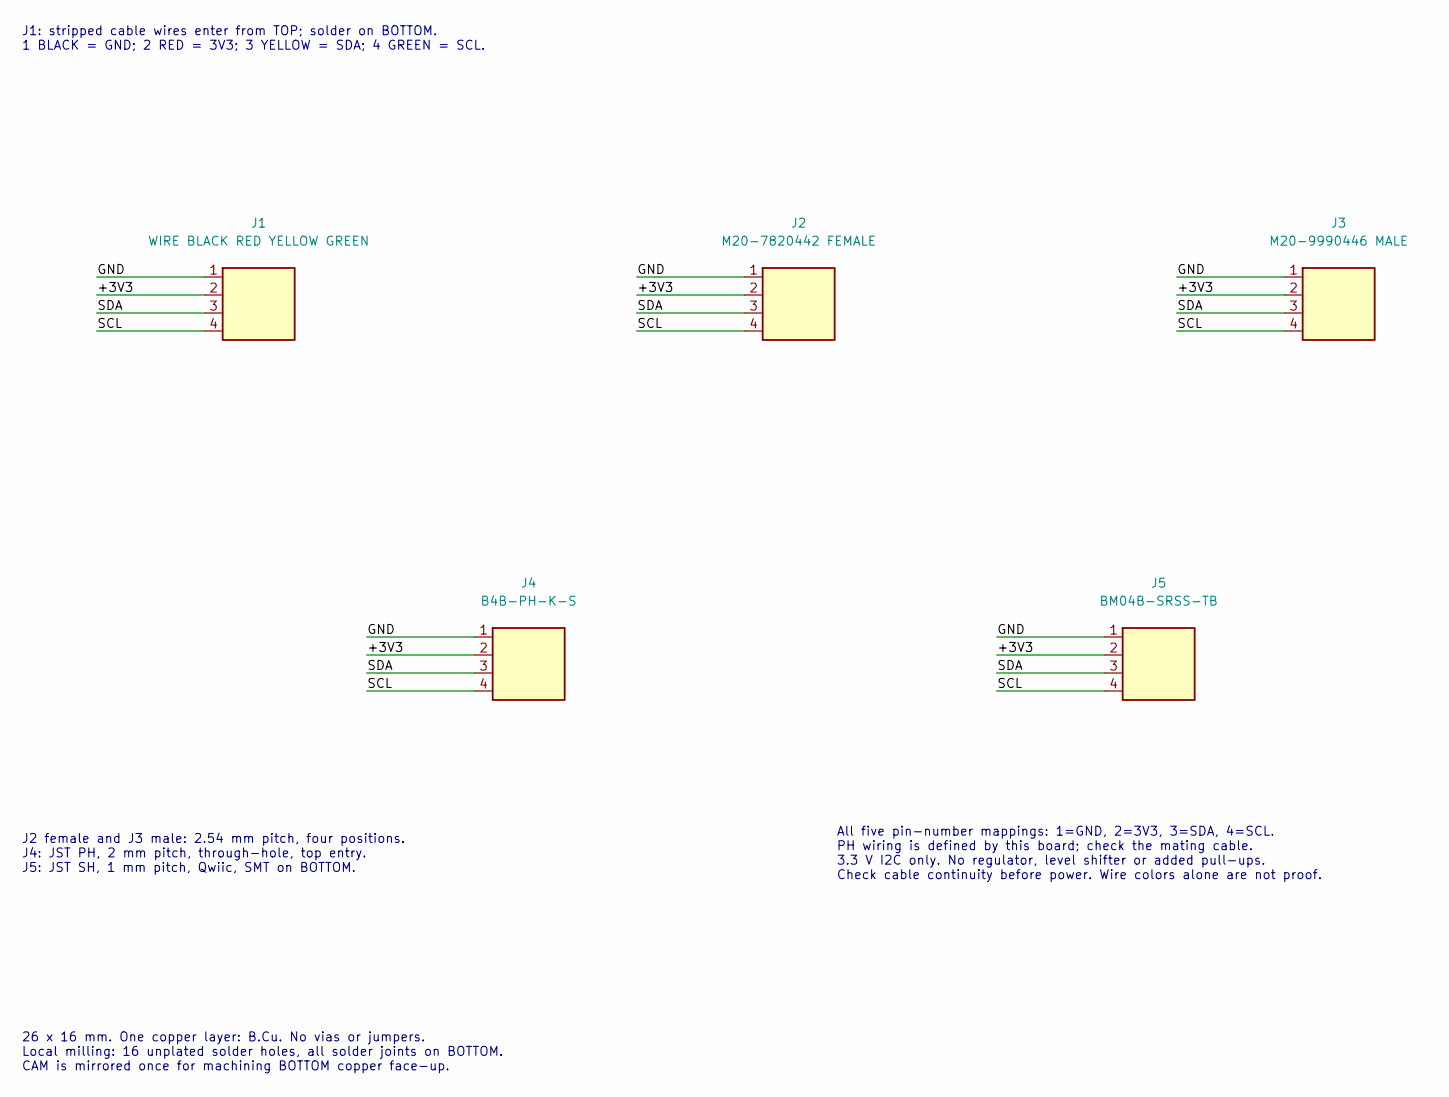
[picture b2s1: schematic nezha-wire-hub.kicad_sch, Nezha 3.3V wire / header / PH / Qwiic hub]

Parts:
J1: WIRE BLACK RED YELLOW GREEN; Wire_1x04_P2.54_D1.10
J2: M20-7820442 FEMALE; Harwin_M20_7820442_Female
J3: M20-9990446 MALE; Harwin_M20_9990446_Male
J4: B4B-PH-K-S; JST_PH_B4B_4_BottomPads_D0.90
J5: BM04B-SRSS-TB; JST_SH_BM04B_SRSS

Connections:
/+3V3: J1.2, J2.2, J3.2, J4.2, J5.2
/GND: J1.1, J2.1, J3.1, J4.1, J5.1
/SCL: J1.4, J2.4, J3.4, J4.4, J5.4
/SDA: J1.3, J2.3, J3.3, J4.3, J5.3

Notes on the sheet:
J1: stripped cable wires enter from TOP; solder on BOTTOM. 1 BLACK = GND; 2 RED = 3V3; 3 YELLOW = SDA; 4 GREEN = SCL.
J2 female and J3 male: 2.54 mm pitch, four positions. J4: JST PH, 2 mm pitch, through-hole, top entry. J5: JST SH, 1 mm pitch, Qwiic, SMT on BOTTOM.
All five pin-number mappings: 1=GND, 2=3V3, 3=SDA, 4=SCL. PH wiring is defined by this board; check the mating cable. 3.3 V I2C only. No regulator, level shifter or added pull-ups. Check cable continuity before power. Wire colors alone are not proof.
26 x 16 mm. One copper layer: B.Cu. No vias or jumpers. Local milling: 16 unplated solder holes, all solder joints on BOTTOM. CAM is mirrored once for machining BOTTOM copper face-up.

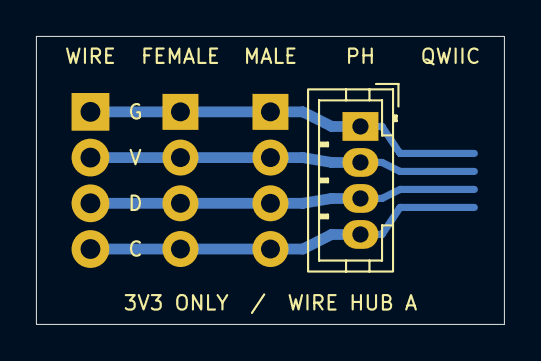
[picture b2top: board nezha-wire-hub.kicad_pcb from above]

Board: 2 copper layers, 26.0 x 16.0 mm, 5 parts (1 on the bottom side), 4 nets.

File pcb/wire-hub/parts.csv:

reference,description,manufacturer,manufacturer_part,per_board,full_panel,notes,supplier_part,url
J1,Four stripped Nezha cable wires,Existing cable,User cable,1,25,1.10 mm holes at 2.54 mm pitch; black red yellow green,,
J2,Female header 1x4 2.54 mm THT,Harwin,M20-7820442,1,25,Top side; 1.05 mm holes,855-M20-7820442,https://www.harwin.com/products/M20-7820442
J3,Male header 1x4 2.54 mm THT,Harwin,M20-9990446,1,25,Top side; 1.05 mm holes,855-M20-9990446,https://www.mouser.com/en/ProductDetail/Harwin/M20-9990446?q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
J4,JST PH 1x4 2.00 mm vertical THT,JST,B4B-PH-K-S(LF)(SN),1,25,Top side; 0.90 mm milled holes; pin1 GND pin2 3V3 pin3 SDA pin4 SCL,455-1706-ND (DigiKey),https://www.digikey.com/en/products/detail/jst-sales-america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
J5,JST SH 1x4 1.00 mm Qwiic socket SMT,JST,BM04B-SRSS-TB(LF)(SN),1,25,BOTTOM side; top-entry socket; cut tape,306-BM04BSRSSTBLFSN,https://www.mouser.com/en/ProductDetail/JST-Commercial/BM04B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
